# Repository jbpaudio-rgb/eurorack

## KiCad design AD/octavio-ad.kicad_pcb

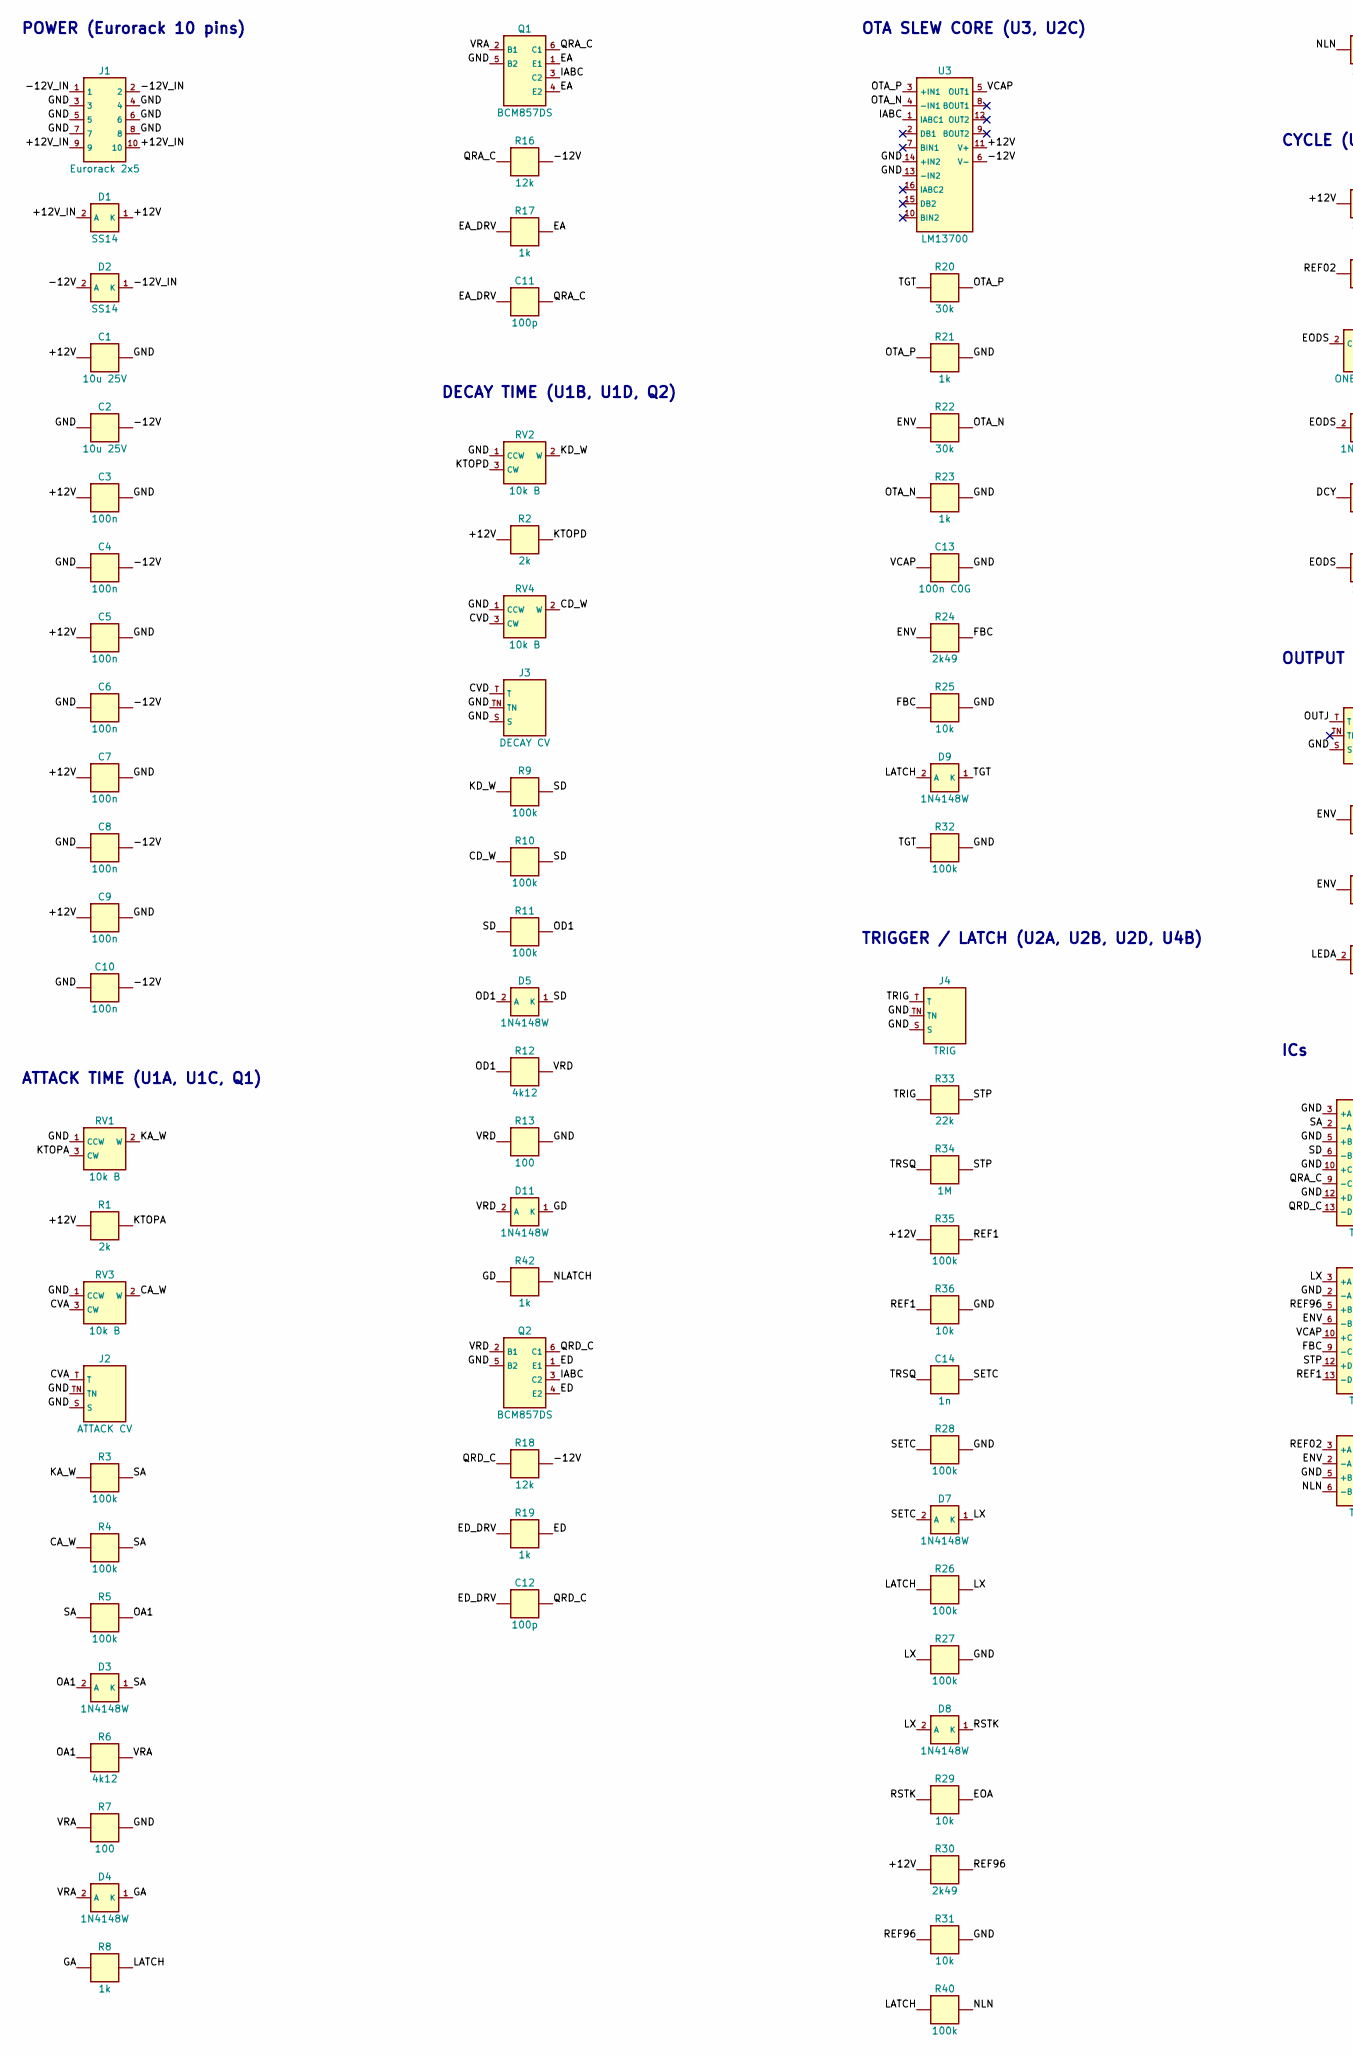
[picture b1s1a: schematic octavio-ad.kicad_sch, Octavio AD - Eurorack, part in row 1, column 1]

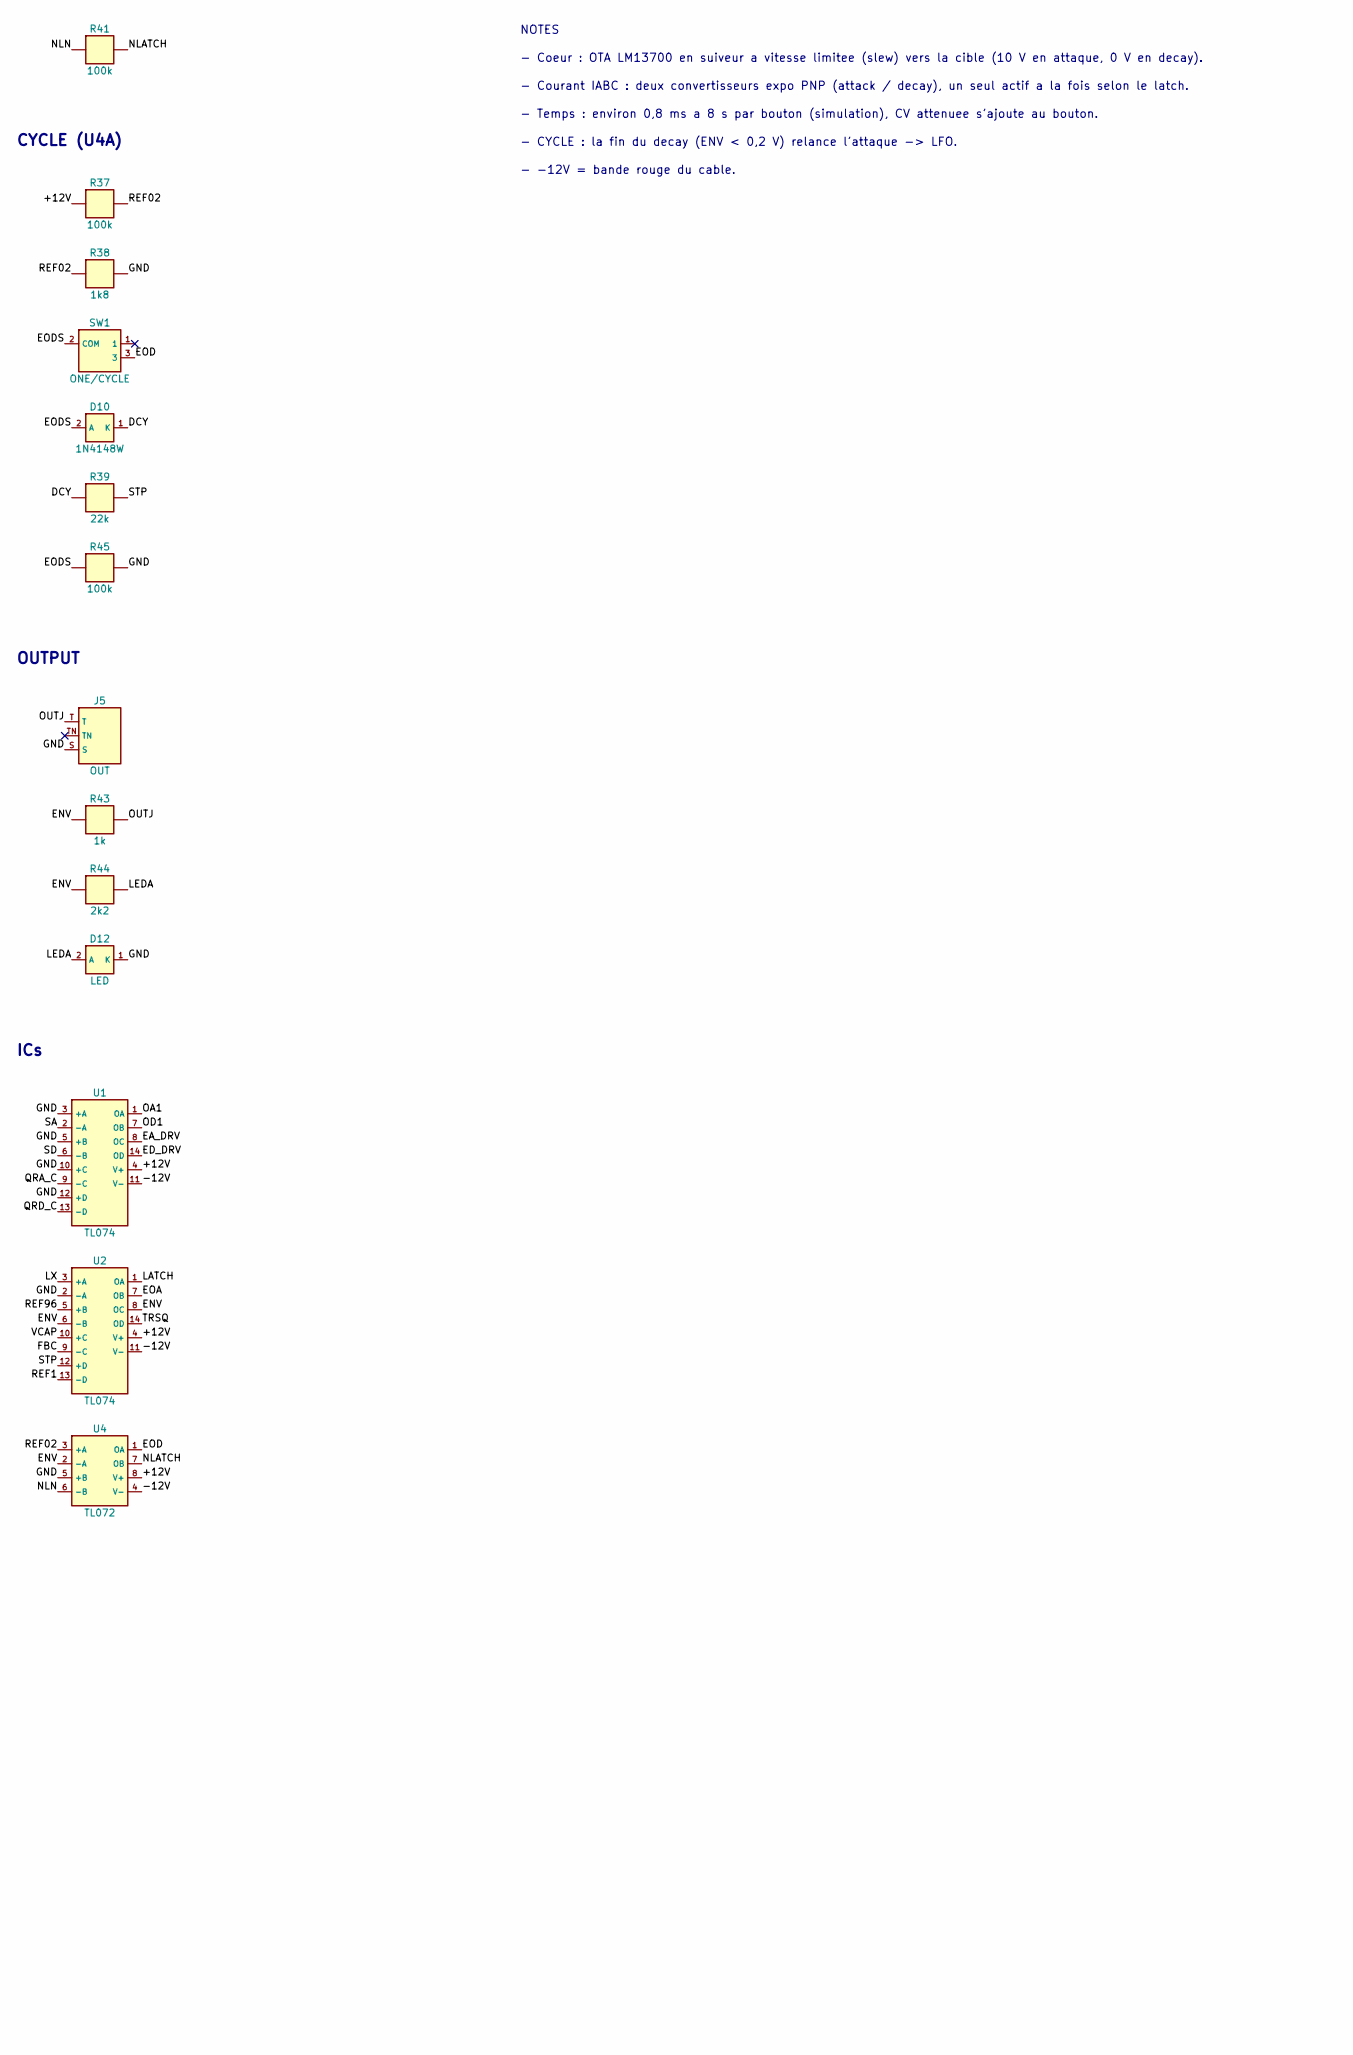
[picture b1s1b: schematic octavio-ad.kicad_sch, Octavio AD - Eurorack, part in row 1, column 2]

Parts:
C1, C2: 10u 25V; C_1206_3216Metric; MPN X5R/X7R 1206
C3, C4, C5, C6, C7, C8, C9, C10: 100n; C_0805_2012Metric
C11, C12: 100p; C_0805_2012Metric
C13: 100n C0G; C_1206_3216Metric; MPN 100 nF C0G/NP0 1206 (condensateur de te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
C14: 1n; C_0805_2012Metric
D1, D2: SS14; D_SMA; MPN SS14 (40 V 1 A Schottky)
D3, D4, D5, D7, D8, D9, D10, D11: 1N4148W; D_SOD-123; MPN 1N4148W
D12: LED; LED_D3.0mm; MPN LED 3 mm rouge
J1: Eurorack 2x5; IDC-Header_2x05_P2.54mm_Vertical; MPN Shrouded header 2x5 2.54 mm
J2: ATTACK CV; Jack_3.5mm_Thonkiconn_PJ398SM; MPN QingPu WQP-PJ301M-12 (Thonkiconn)
J3: DECAY CV; Jack_3.5mm_Thonkiconn_PJ398SM; MPN QingPu WQP-PJ301M-12 (Thonkiconn)
J4: TRIG; Jack_3.5mm_Thonkiconn_PJ398SM; MPN QingPu WQP-PJ301M-12 (Thonkiconn)
J5: OUT; Jack_3.5mm_Thonkiconn_PJ398SM; MPN QingPu WQP-PJ301M-12 (Thonkiconn)
Q1, Q2: BCM857DS; SOT-457; MPN BCM857DS (paire PNP appairée)
R1, R2: 2k; R_0805_2012Metric
R3, R4, R5, R9, R10, R11, R26, R27, R28, R32, R35, R37, R40, R41, R45: 100k; R_0805_2012Metric
R6, R12: 4k12; R_0805_2012Metric
R7, R13: 100; R_0805_2012Metric
R8, R17, R19, R21, R23, R42, R43: 1k; R_0805_2012Metric
R16, R18: 12k; R_0805_2012Metric
R20, R22: 30k; R_0805_2012Metric
R24, R30: 2k49; R_0805_2012Metric
R25, R29, R31, R36: 10k; R_0805_2012Metric
R33, R39: 22k; R_0805_2012Metric
R34: 1M; R_0805_2012Metric
R38: 1k8; R_0805_2012Metric
R44: 2k2; R_0805_2012Metric
RV1, RV2, RV3, RV4: 10k B; Pot_Alpha_9mm_Vertical; MPN POT-R09V-10K (9 mm vertical, B10k)
SW1: ONE/CYCLE; Toggle_SPDT_Dailywell_2MS1; MPN C&K T101MH9ABE (SPDT ON-ON, PC pin)
U1, U2: TL074; SOIC-14_3.9x8.7mm_P1.27mm; MPN TL074CDR
U3: LM13700; SOIC-16_3.9x9.9mm_P1.27mm; MPN LM13700MX/NOPB
U4: TL072; SOIC-8_3.9x4.9mm_P1.27mm; MPN TL072CDR

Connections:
+12V: C1.1, C3.1, C5.1, C7.1, C9.1, D1.1 (K), R1.1, R2.1, R30.1, R35.1, R37.1, U1.4 (V+), U2.4 (V+), U3.11 (V+), U4.8 (V+)
+12V_IN: D1.2 (A), J1.9, J1.10
-12V: C2.2, C4.2, C6.2, C8.2, C10.2, D2.2 (A), R16.2, R18.2, U1.11 (V-), U2.11 (V-), U3.6 (V-), U4.4 (V-)
-12V_IN: D2.1 (K), J1.1, J1.2
CA_W: R4.1, RV3.2 (W)
CD_W: R10.1, RV4.2 (W)
CVA: J2.T, RV3.3 (CW)
CVD: J3.T, RV4.3 (CW)
DCY: D10.1 (K), R39.1
EA: Q1.1 (E1), Q1.4 (E2), R17.2
EA_DRV: C11.1, R17.1, U1.8 (OC)
ED: Q2.1 (E1), Q2.4 (E2), R19.2
ED_DRV: C12.1, R19.1, U1.14 (OD)
ENV: R22.1, R24.1, R43.1, R44.1, U2.6 (-B), U2.8 (OC), U4.2 (-A)
EOA: R29.2, U2.7 (OB)
EOD: SW1.3, U4.1 (OA)
EODS: D10.2 (A), R45.1, SW1.2 (COM)
FBC: R24.2, R25.1, U2.9 (-C)
GA: D4.1 (K), R8.1
GD: D11.1 (K), R42.1
GND: C1.2, C2.1, C3.2, C4.1, C5.2, C6.1, C7.2, C8.1, C9.2, C10.1, C13.2, D12.1 (K), J1.3, J1.4, J1.5, J1.6, J1.7, J1.8, J2.S, J2.TN, J3.S, J3.TN, J4.S, J4.TN, J5.S, Q1.5 (B2), Q2.5 (B2), R7.2, R13.2, R21.2, R23.2, R25.2, R27.2, R28.2, R31.2, R32.2, R36.2, R38.2, R45.2, RV1.1 (CCW), RV2.1 (CCW), RV3.1 (CCW), RV4.1 (CCW), U1.3 (+A), U1.5 (+B), U1.10 (+C), U1.12 (+D), U2.2 (-A), U3.13 (-IN2), U3.14 (+IN2), U4.5 (+B)
IABC: Q1.3 (C2), Q2.3 (C2), U3.1 (IABC1)
KA_W: R3.1, RV1.2 (W)
KD_W: R9.1, RV2.2 (W)
KTOPA: R1.2, RV1.3 (CW)
KTOPD: R2.2, RV2.3 (CW)
LATCH: D9.2 (A), R8.2, R26.1, R40.1, U2.1 (OA)
LEDA: D12.2 (A), R44.2
LX: D7.1 (K), D8.2 (A), R26.2, R27.1, U2.3 (+A)
NLATCH: R41.2, R42.2, U4.7 (OB)
NLN: R40.2, R41.1, U4.6 (-B)
OA1: D3.2 (A), R5.2, R6.1, U1.1 (OA)
OD1: D5.2 (A), R11.2, R12.1, U1.7 (OB)
OTA_N: R22.2, R23.1, U3.4 (-IN1)
OTA_P: R20.2, R21.1, U3.3 (+IN1)
OUTJ: J5.T, R43.2
QRA_C: C11.2, Q1.6 (C1), R16.1, U1.9 (-C)
QRD_C: C12.2, Q2.6 (C1), R18.1, U1.13 (-D)
REF1: R35.2, R36.1, U2.13 (-D)
REF02: R37.2, R38.1, U4.3 (+A)
REF96: R30.2, R31.1, U2.5 (+B)
RSTK: D8.1 (K), R29.1
SA: D3.1 (K), R3.2, R4.2, R5.1, U1.2 (-A)
SD: D5.1 (K), R9.2, R10.2, R11.1, U1.6 (-B)
SETC: C14.2, D7.2 (A), R28.1
STP: R33.2, R34.2, R39.2, U2.12 (+D)
TGT: D9.1 (K), R20.1, R32.1
TRIG: J4.T, R33.1
TRSQ: C14.1, R34.1, U2.14 (OD)
VCAP: C13.1, U2.10 (+C), U3.5 (OUT1)
VRA: D4.2 (A), Q1.2 (B1), R6.2, R7.1
VRD: D11.2 (A), Q2.2 (B1), R12.2, R13.1

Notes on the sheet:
POWER (Eurorack 10 pins)
ATTACK TIME (U1A, U1C, Q1)
DECAY TIME (U1B, U1D, Q2)
OTA SLEW CORE (U3, U2C)
TRIGGER / LATCH (U2A, U2B, U2D, U4B)
CYCLE (U4A)
OUTPUT
ICs
NOTES
- Coeur : OTA LM13700 en suiveur a vitesse limitee (slew) vers la cible (10 V en attaque, 0 V en decay).
- Courant IABC : deux convertisseurs expo PNP (attack / decay), un seul actif a la fois selon le latch.
- Temps : environ 0,8 ms a 8 s par bouton (simulation), CV attenuee s'ajoute au bouton.
- CYCLE : la fin du decay (ENV < 0,2 V) relance l'attaque -> LFO.
- -12V = bande rouge du cable.

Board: 2 copper layers, 84 parts (74 on the bottom side), 52 nets, no tracks yet.

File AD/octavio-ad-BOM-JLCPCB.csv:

Comment,Designator,Footprint,LCSC Part #,Notes
10u 25V X5R/X7R 1206,"C1,C2",C_1206_3216Metric,,X5R/X7R 1206 - SMT bottom - laisser JLC choisir (Basic de preference)
100p,"C11,C12",C_0805_2012Metric,,SMT bottom - laisser JLC choisir (Basic de preference)
100n C0G 100 nF C0G/NP0 1206,C13,C_1206_3216Metric,,100 nF C0G/NP0 1206 (condensateur de temps) - SMT bottom - laisser JLC choisir (Basic de preference)
1n,C14,C_0805_2012Metric,,SMT bottom - laisser JLC choisir (Basic de preference)
100n,"C3,C4,C5,C6,C7,C8,C9,C10",C_0805_2012Metric,,SMT bottom - laisser JLC choisir (Basic de preference)
SS14,"D1,D2",D_SMA,,SS14 (40 V 1 A Schottky) - SMT bottom - laisser JLC choisir (Basic de preference)
LED,D12,LED_D3.0mm,,LED 3 mm rouge - THT (wave soldering) - laisser JLC choisir (Basic de preference)
1N4148W,"D3,D4,D5,D11,D9,D7,D8,D10",D_SOD-123,,1N4148W - SMT bottom - laisser JLC choisir (Basic de preference)
Eurorack 2x5,J1,IDC-Header_2x05_P2.54mm_Vertical,,Shrouded header 2x5 2.54 mm - THT (wave soldering) - laisser JLC choisir (Basic de preference)
ATTACK CV,J2,Jack_3.5mm_Thonkiconn_PJ398SM,C9900080080,QingPu WQP-PJ301M-12 (Thonkiconn) - THT (wave soldering)
DECAY CV,J3,Jack_3.5mm_Thonkiconn_PJ398SM,C9900080080,QingPu WQP-PJ301M-12 (Thonkiconn) - THT (wave soldering)
TRIG,J4,Jack_3.5mm_Thonkiconn_PJ398SM,C9900080080,QingPu WQP-PJ301M-12 (Thonkiconn) - THT (wave soldering)
OUT,J5,Jack_3.5mm_Thonkiconn_PJ398SM,C9900080080,QingPu WQP-PJ301M-12 (Thonkiconn) - THT (wave soldering)
BCM857DS,"Q1,Q2",SOT-457,,BCM857DS (paire PNP appairée) - SMT bottom - laisser JLC choisir (Basic de preference)
2k 1% 0805,"R1,R2",R_0805_2012Metric,,SMT bottom - laisser JLC choisir (Basic de preference)
12k 1% 0805,"R16,R18",R_0805_2012Metric,,SMT bottom - laisser JLC choisir (Basic de preference)
30k 1% 0805,"R20,R22",R_0805_2012Metric,,SMT bottom - laisser JLC choisir (Basic de preference)
2k49 1% 0805,"R24,R30",R_0805_2012Metric,,SMT bottom - laisser JLC choisir (Basic de preference)
10k 1% 0805,"R25,R36,R29,R31",R_0805_2012Metric,,SMT bottom - laisser JLC choisir (Basic de preference)
100k 1% 0805,"R3,R4,R5,R9,R10,R11,R32,R35,R28,R26,R27,R40,R41,R37,R45",R_0805_2012Metric,,SMT bottom - laisser JLC choisir (Basic de preference)
22k 1% 0805,"R33,R39",R_0805_2012Metric,,SMT bottom - laisser JLC choisir (Basic de preference)
1M 1% 0805,R34,R_0805_2012Metric,,SMT bottom - laisser JLC choisir (Basic de preference)
1k8 1% 0805,R38,R_0805_2012Metric,,SMT bottom - laisser JLC choisir (Basic de preference)
2k2 1% 0805,R44,R_0805_2012Metric,,SMT bottom - laisser JLC choisir (Basic de preference)
4k12 1% 0805,"R6,R12",R_0805_2012Metric,,SMT bottom - laisser JLC choisir (Basic de preference)
100 1% 0805,"R7,R13",R_0805_2012Metric,,SMT bottom - laisser JLC choisir (Basic de preference)
1k 1% 0805,"R8,R17,R42,R19,R21,R23,R43",R_0805_2012Metric,,SMT bottom - laisser JLC choisir (Basic de preference)
10k B,"RV1,RV2,RV3,RV4",Pot_Alpha_9mm_Vertical,,"POT-R09V-10K (9 mm vertical, B10k) - THT (wave soldering) - laisser JLC choisir (Basic de preference)"
ONE/CYCLE,SW1,Toggle_SPDT_Dailywell_2MS1,C668578,"C&K T101MH9ABE (SPDT ON-ON, PC pin) - THT (wave soldering)"
TL074CDR,"U1,U2",SOIC-14_3.9x8.7mm_P1.27mm,C12594,TL074CDR - SMT bottom
LM13700MX/NOPB,U3,SOIC-16_3.9x9.9mm_P1.27mm,,LM13700MX/NOPB - SMT bottom - laisser JLC choisir (Basic de preference)
TL072CDR,U4,SOIC-8_3.9x4.9mm_P1.27mm,,TL072CDR - SMT bottom - laisser JLC choisir (Basic de preference)

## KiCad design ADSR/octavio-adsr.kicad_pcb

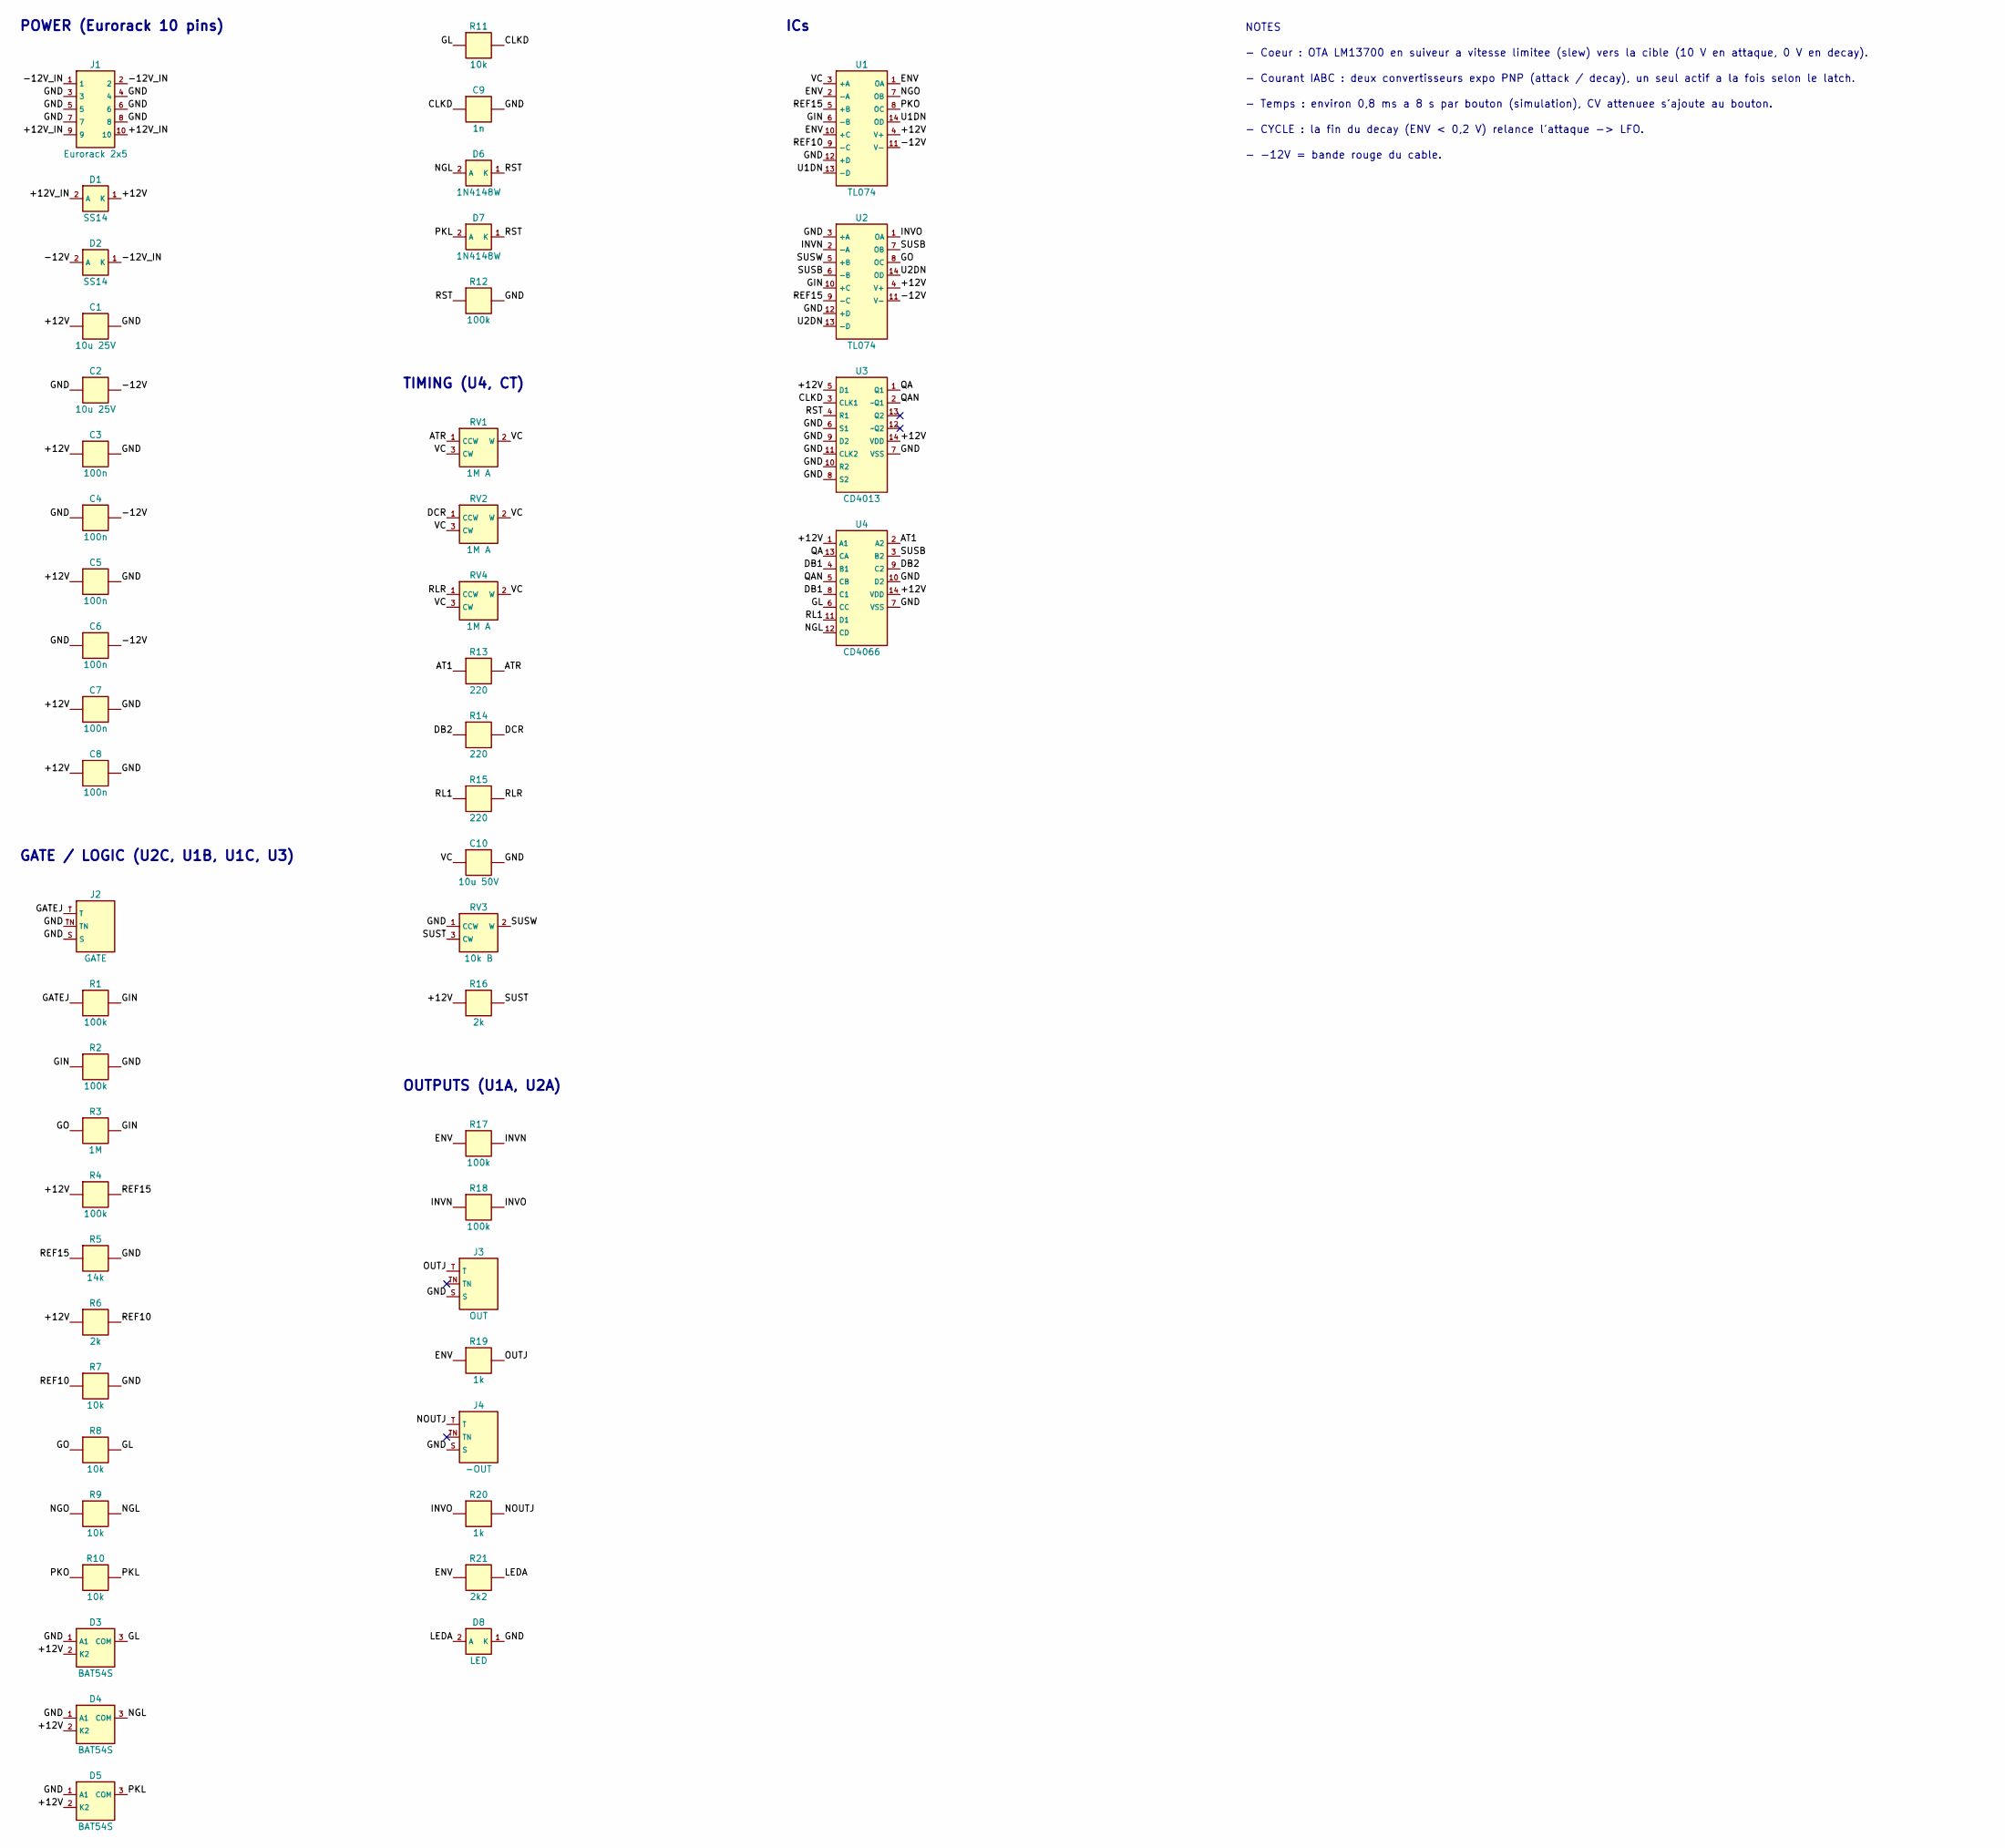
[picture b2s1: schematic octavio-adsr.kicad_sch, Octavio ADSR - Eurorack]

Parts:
C1, C2: 10u 25V; C_1206_3216Metric; MPN X5R/X7R 1206
C3, C4, C5, C6, C7, C8: 100n; C_0805_2012Metric
C9: 1n; C_0805_2012Metric
C10: 10u 50V; C_1206_3216Metric; MPN 10 µF 50 V X7R 1206 (condensateur de te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
D1, D2: SS14; D_SMA; MPN SS14 (40 V 1 A Schottky)
D3, D4, D5: BAT54S; SOT-23; MPN BAT54S (clamp 0..12 V)
D6, D7: 1N4148W; D_SOD-123; MPN 1N4148W
D8: LED; LED_D3.0mm; MPN LED 3 mm rouge
J1: Eurorack 2x5; IDC-Header_2x05_P2.54mm_Vertical; MPN Shrouded header 2x5 2.54 mm
J2: GATE; Jack_3.5mm_Thonkiconn_PJ398SM; MPN QingPu WQP-PJ301M-12 (Thonkiconn)
J3: OUT; Jack_3.5mm_Thonkiconn_PJ398SM; MPN QingPu WQP-PJ301M-12 (Thonkiconn)
J4: -OUT; Jack_3.5mm_Thonkiconn_PJ398SM; MPN QingPu WQP-PJ301M-12 (Thonkiconn)
R1, R2, R4, R12, R17, R18: 100k; R_0805_2012Metric
R3: 1M; R_0805_2012Metric
R5: 14k; R_0805_2012Metric
R6, R16: 2k; R_0805_2012Metric
R7, R8, R9, R10, R11: 10k; R_0805_2012Metric
R13, R14, R15: 220; R_0805_2012Metric
R19, R20: 1k; R_0805_2012Metric
R21: 2k2; R_0805_2012Metric
RV1, RV2, RV4: 1M A; Pot_Alpha_9mm_Vertical; MPN Alpha RV09 1M A (log) - à confirmer LCSC
RV3: 10k B; Pot_Alpha_9mm_Vertical; MPN POT-R09V-10K (9 mm vertical, B10k)
U1, U2: TL074; SOIC-14_3.9x8.7mm_P1.27mm; MPN TL074CDR
U3: CD4013; SOIC-14_3.9x8.7mm_P1.27mm; MPN CD4013BM96
U4: CD4066; SOIC-14_3.9x8.7mm_P1.27mm; MPN CD4066BM96

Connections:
+12V: C1.1, C3.1, C5.1, C7.1, C8.1, D1.1 (K), D3.2 (K2), D4.2 (K2), D5.2 (K2), R4.1, R6.1, R16.1, U1.4 (V+), U2.4 (V+), U3.5 (D1), U3.14 (VDD), U4.1 (A1), U4.14 (VDD)
+12V_IN: D1.2 (A), J1.9, J1.10
-12V: C2.2, C4.2, C6.2, D2.2 (A), U1.11 (V-), U2.11 (V-)
-12V_IN: D2.1 (K), J1.1, J1.2
AT1: R13.1, U4.2 (A2)
ATR: R13.2, RV1.1 (CCW)
CLKD: C9.1, R11.2, U3.3 (CLK1)
DB1: U4.4 (B1), U4.8 (C1)
DB2: R14.1, U4.9 (C2)
DCR: R14.2, RV2.1 (CCW)
ENV: R17.1, R19.1, R21.1, U1.1 (OA), U1.2 (-A), U1.10 (+C)
GATEJ: J2.T, R1.1
GIN: R1.2, R2.1, R3.2, U1.6 (-B), U2.10 (+C)
GL: D3.3 (COM), R8.2, R11.1, U4.6 (CC)
GND: C1.2, C2.1, C3.2, C4.1, C5.2, C6.1, C7.2, C8.2, C9.2, C10.2, D3.1 (A1), D4.1 (A1), D5.1 (A1), D8.1 (K), J1.3, J1.4, J1.5, J1.6, J1.7, J1.8, J2.S, J2.TN, J3.S, J4.S, R2.2, R5.2, R7.2, R12.2, RV3.1 (CCW), U1.12 (+D), U2.3 (+A), U2.12 (+D), U3.6 (S1), U3.7 (VSS), U3.8 (S2), U3.9 (D2), U3.10 (R2), U3.11 (CLK2), U4.7 (VSS), U4.10 (D2)
GO: R3.1, R8.1, U2.8 (OC)
INVN: R17.2, R18.1, U2.2 (-A)
INVO: R18.2, R20.1, U2.1 (OA)
LEDA: D8.2 (A), R21.2
NGL: D4.3 (COM), D6.2 (A), R9.2, U4.12 (CD)
NGO: R9.1, U1.7 (OB)
NOUTJ: J4.T, R20.2
OUTJ: J3.T, R19.2
PKL: D5.3 (COM), D7.2 (A), R10.2
PKO: R10.1, U1.8 (OC)
QA: U3.1 (Q1), U4.13 (CA)
QAN: U3.2 (~Q1), U4.5 (CB)
REF10: R6.2, R7.1, U1.9 (-C)
REF15: R4.2, R5.1, U1.5 (+B), U2.9 (-C)
RL1: R15.1, U4.11 (D1)
RLR: R15.2, RV4.1 (CCW)
RST: D6.1 (K), D7.1 (K), R12.1, U3.4 (R1)
SUSB: U2.6 (-B), U2.7 (OB), U4.3 (B2)
SUST: R16.2, RV3.3 (CW)
SUSW: RV3.2 (W), U2.5 (+B)
U1DN: U1.13 (-D), U1.14 (OD)
U2DN: U2.13 (-D), U2.14 (OD)
VC: C10.1, RV1.2 (W), RV1.3 (CW), RV2.2 (W), RV2.3 (CW), RV4.2 (W), RV4.3 (CW), U1.3 (+A)

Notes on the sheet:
POWER (Eurorack 10 pins)
GATE / LOGIC (U2C, U1B, U1C, U3)
TIMING (U4, CT)
OUTPUTS (U1A, U2A)
ICs
NOTES
- Coeur : OTA LM13700 en suiveur a vitesse limitee (slew) vers la cible (10 V en attaque, 0 V en decay).
- Courant IABC : deux convertisseurs expo PNP (attack / decay), un seul actif a la fois selon le latch.
- Temps : environ 0,8 ms a 8 s par bouton (simulation), CV attenuee s'ajoute au bouton.
- CYCLE : la fin du decay (ENV < 0,2 V) relance l'attaque -> LFO.
- -12V = bande rouge du cable.

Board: 2 copper layers, 51 parts (43 on the bottom side), 38 nets, no tracks yet.

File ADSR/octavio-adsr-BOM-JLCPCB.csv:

Comment,Designator,Footprint,LCSC Part #,Notes
10u 25V X5R/X7R 1206,"C1,C2",C_1206_3216Metric,,X5R/X7R 1206 - SMT bottom - laisser JLC choisir (Basic de preference)
10u 50V 10 µF 50 V X7R 1206,C10,C_1206_3216Metric,,10 µF 50 V X7R 1206 (condensateur de temps) - SMT bottom - laisser JLC choisir (Basic de preference)
100n,"C3,C4,C5,C6,C7,C8",C_0805_2012Metric,,SMT bottom - laisser JLC choisir (Basic de preference)
1n,C9,C_0805_2012Metric,,SMT bottom - laisser JLC choisir (Basic de preference)
SS14,"D1,D2",D_SMA,,SS14 (40 V 1 A Schottky) - SMT bottom - laisser JLC choisir (Basic de preference)
BAT54S,"D3,D4,D5",SOT-23,,BAT54S (clamp 0..12 V) - SMT bottom - laisser JLC choisir (Basic de preference)
1N4148W,"D6,D7",D_SOD-123,,1N4148W - SMT bottom - laisser JLC choisir (Basic de preference)
LED,D8,LED_D3.0mm,,LED 3 mm rouge - THT (wave soldering) - laisser JLC choisir (Basic de preference)
Eurorack 2x5,J1,IDC-Header_2x05_P2.54mm_Vertical,,Shrouded header 2x5 2.54 mm - THT (wave soldering) - laisser JLC choisir (Basic de preference)
GATE,J2,Jack_3.5mm_Thonkiconn_PJ398SM,C9900080080,QingPu WQP-PJ301M-12 (Thonkiconn) - THT (wave soldering)
OUT,J3,Jack_3.5mm_Thonkiconn_PJ398SM,C9900080080,QingPu WQP-PJ301M-12 (Thonkiconn) - THT (wave soldering)
-OUT,J4,Jack_3.5mm_Thonkiconn_PJ398SM,C9900080080,QingPu WQP-PJ301M-12 (Thonkiconn) - THT (wave soldering)
100k 1% 0805,"R1,R2,R4,R12,R17,R18",R_0805_2012Metric,,SMT bottom - laisser JLC choisir (Basic de preference)
220 1% 0805,"R13,R14,R15",R_0805_2012Metric,,SMT bottom - laisser JLC choisir (Basic de preference)
1k 1% 0805,"R19,R20",R_0805_2012Metric,,SMT bottom - laisser JLC choisir (Basic de preference)
2k2 1% 0805,R21,R_0805_2012Metric,,SMT bottom - laisser JLC choisir (Basic de preference)
1M 1% 0805,R3,R_0805_2012Metric,,SMT bottom - laisser JLC choisir (Basic de preference)
14k 1% 0805,R5,R_0805_2012Metric,,SMT bottom - laisser JLC choisir (Basic de preference)
2k 1% 0805,"R6,R16",R_0805_2012Metric,,SMT bottom - laisser JLC choisir (Basic de preference)
10k 1% 0805,"R7,R8,R9,R10,R11",R_0805_2012Metric,,SMT bottom - laisser JLC choisir (Basic de preference)
1M A,"RV1,RV2,RV4",Pot_Alpha_9mm_Vertical,,Alpha RV09 1M A (log) - à confirmer LCSC - THT (wave soldering) - laisser JLC choisir (Basic de preference)
10k B,RV3,Pot_Alpha_9mm_Vertical,,"POT-R09V-10K (9 mm vertical, B10k) - THT (wave soldering) - laisser JLC choisir (Basic de preference)"
TL074CDR,"U1,U2",SOIC-14_3.9x8.7mm_P1.27mm,C12594,TL074CDR - SMT bottom
CD4013BM96,U3,SOIC-14_3.9x8.7mm_P1.27mm,,CD4013BM96 - SMT bottom - laisser JLC choisir (Basic de preference)
CD4066BM96,U4,SOIC-14_3.9x8.7mm_P1.27mm,,CD4066BM96 - SMT bottom - laisser JLC choisir (Basic de preference)
